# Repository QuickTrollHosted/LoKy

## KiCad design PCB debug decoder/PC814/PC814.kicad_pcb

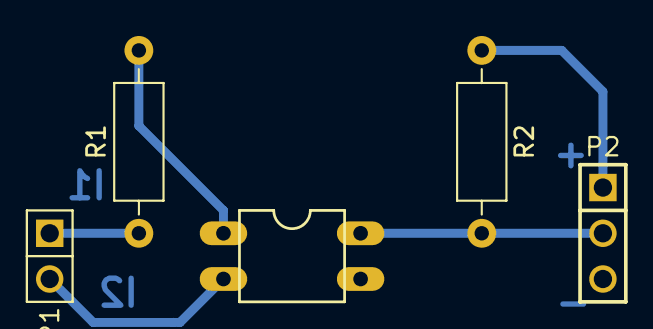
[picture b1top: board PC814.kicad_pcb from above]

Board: 2 copper layers, 5 parts (0 on the bottom side), 6 nets.

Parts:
OK1: PC814; DIL04
P1: H1; HEADER_M_2.54MM_1R2P_ST_AU_PTH
P2: H2; HEADER_M_2.54MM_1R3P_ST_AU_PTH
R1, R2: R; R_Axial_DIN0207_L6.3mm_D2.5mm_P10.16mm_Horizontal

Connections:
/3V3: P2.1, R2.1
/GND: OK1.3, P2.3
unnamed: OK1.1, R1.2
unnamed: OK1.2, P1.2
unnamed: OK1.4, P2.2, R2.2
unnamed: P1.1, R1.1

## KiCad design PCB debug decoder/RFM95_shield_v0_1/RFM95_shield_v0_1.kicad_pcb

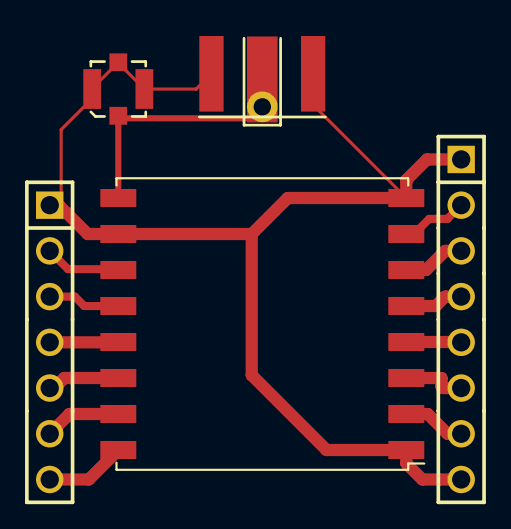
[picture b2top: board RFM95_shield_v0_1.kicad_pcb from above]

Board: 2 copper layers, 6 parts (0 on the bottom side), 13 nets.

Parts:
AE1: Antenna_Helical_RA; ANTENNA_HELICAL_RA
J1: u.FL; U.FL-R-SMT
J2: SMA; SMA_EDGE
P1: H1; HEADER_M_2.54MM_1R7P_ST_AU_PTH
P2: H2; HEADER_M_2.54MM_1R8P_ST_AU_PTH
U1: RFM95; HOPERF_RFM9XW_SMD

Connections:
/3V3: P1.4, U1.13
/DIO0: P1.5, U1.14
/DIO1: P1.6, U1.15
/DIO2: P1.7, U1.16
/GND: J1.2, J1.3, J1.4, J2.2, J2.3, P1.1, P2.1, P2.8, U1.1, U1.8, U1.10
/MISO: P2.7, U1.2
/MOSI: P2.6, U1.3
/NSS: P2.4, U1.5
/RST: P2.3, U1.6
/SCK: P2.5, U1.4
unnamed: P1.2, U1.11
unnamed: P1.3, U1.12
unnamed: P2.2, U1.7

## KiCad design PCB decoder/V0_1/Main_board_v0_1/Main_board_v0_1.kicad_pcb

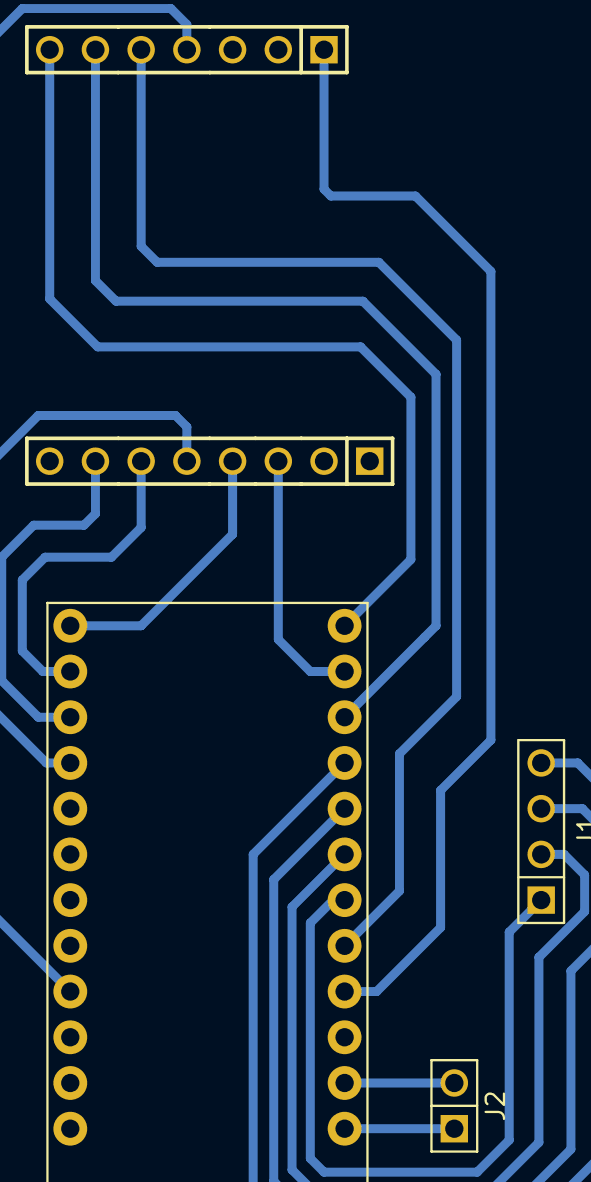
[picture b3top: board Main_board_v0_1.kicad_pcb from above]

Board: 2 copper layers, 5 parts (0 on the bottom side), 17 nets.

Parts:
J1: H1; HEADER_F_2.54MM_1R4P_ST_SN_PTH
J2: H2; HEADER_F_2.54MM_1R2P_ST_AU_PTH
P1: H1; HEADER_M_2.54MM_1R7P_ST_AU_PTH
P2: H2; HEADER_M_2.54MM_1R8P_ST_AU_PTH
U1: ARDUINO_PRO_MINI; MODULE_ARDUINO_PRO_MINI

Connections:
/3V3: P1.4, U1.JP6_4
/DIO0: P1.5, U1.JP7_8
/DIO1: P1.6, U1.JP7_3
/DIO2: P1.7, U1.JP7_1
/GND: P1.1, U1.JP7_9
/MISO: P2.7, U1.JP6_10
/MOSI: P2.6, U1.JP6_11
/NSS: P2.4, U1.JP6_12
/RST: P2.3, U1.JP7_2
/SCK: P2.5, U1.JP6_9
unnamed: J1.1, U1.JP7_7
unnamed: J1.2, U1.JP7_6
unnamed: J1.3, U1.JP7_5
unnamed: J1.4, U1.JP7_4
unnamed: J2.1, U1.JP7_12
unnamed: J2.2, U1.JP7_11
unnamed: U1.JP1_5, U1.JP1_6

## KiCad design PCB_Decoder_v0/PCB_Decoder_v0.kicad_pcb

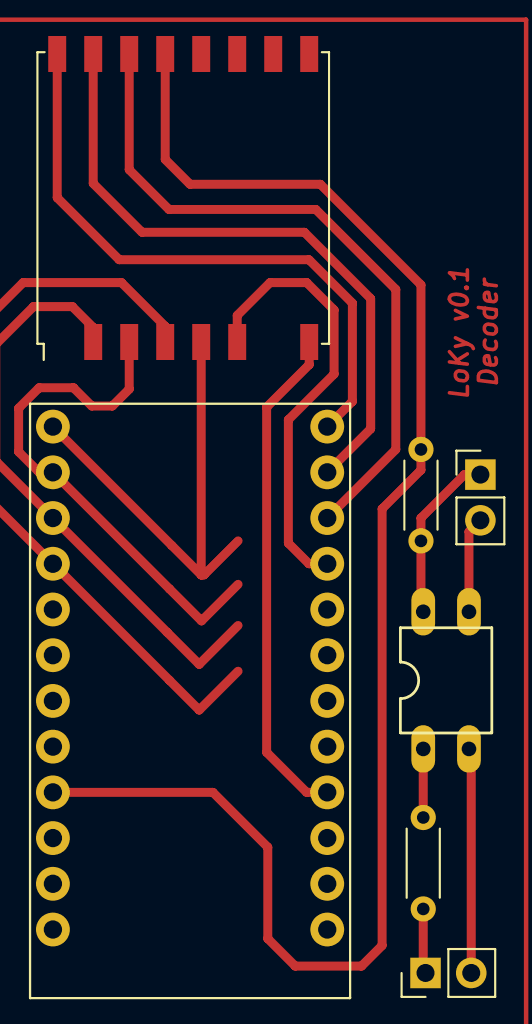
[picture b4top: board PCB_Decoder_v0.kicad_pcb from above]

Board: 2 copper layers, 7 parts (0 on the bottom side), 16 nets.

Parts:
 : PC814; DIL04
J1, J2: PinHeader_1x02_P2.54mm_Vertical
R1: 1.2K; R_Axial_DIN0204_L3.6mm_D1.6mm_P5.08mm_Horizontal
R3: 3.3K; R_Axial_DIN0204_L3.6mm_D1.6mm_P5.08mm_Horizontal
U1: PRO_MINI; MODULE_ARDUINO_PRO_MINI
U2: RFM95W; HOPERF_RFM9XW_SMD

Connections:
+3V3: R3.1, U1.JP6_4, U2.13
/DIO0: U1.JP7_3, U2.14
/DIO1: U1.JP7_2, U2.15
/DIO2: U1.JP7_1, U2.16
/MISO: U1.JP6_10, U2.2
/MOSI: U1.JP6_11, U2.3
/RST: U1.JP7_4, U2.6
/SCK: U1.JP6_9, U2.4
/SS: U1.JP6_12, U2.5
/infoTIC_GND: .3, J2.2
/infoTIC_TX: .4, J2.1, R3.2
GNDREF: U1.JP7_9, U2.8
unnamed: J1.1, R1.2
unnamed: .2, J1.2
unnamed: .1, R1.1
unnamed: U1.JP1_5, U1.JP1_6
